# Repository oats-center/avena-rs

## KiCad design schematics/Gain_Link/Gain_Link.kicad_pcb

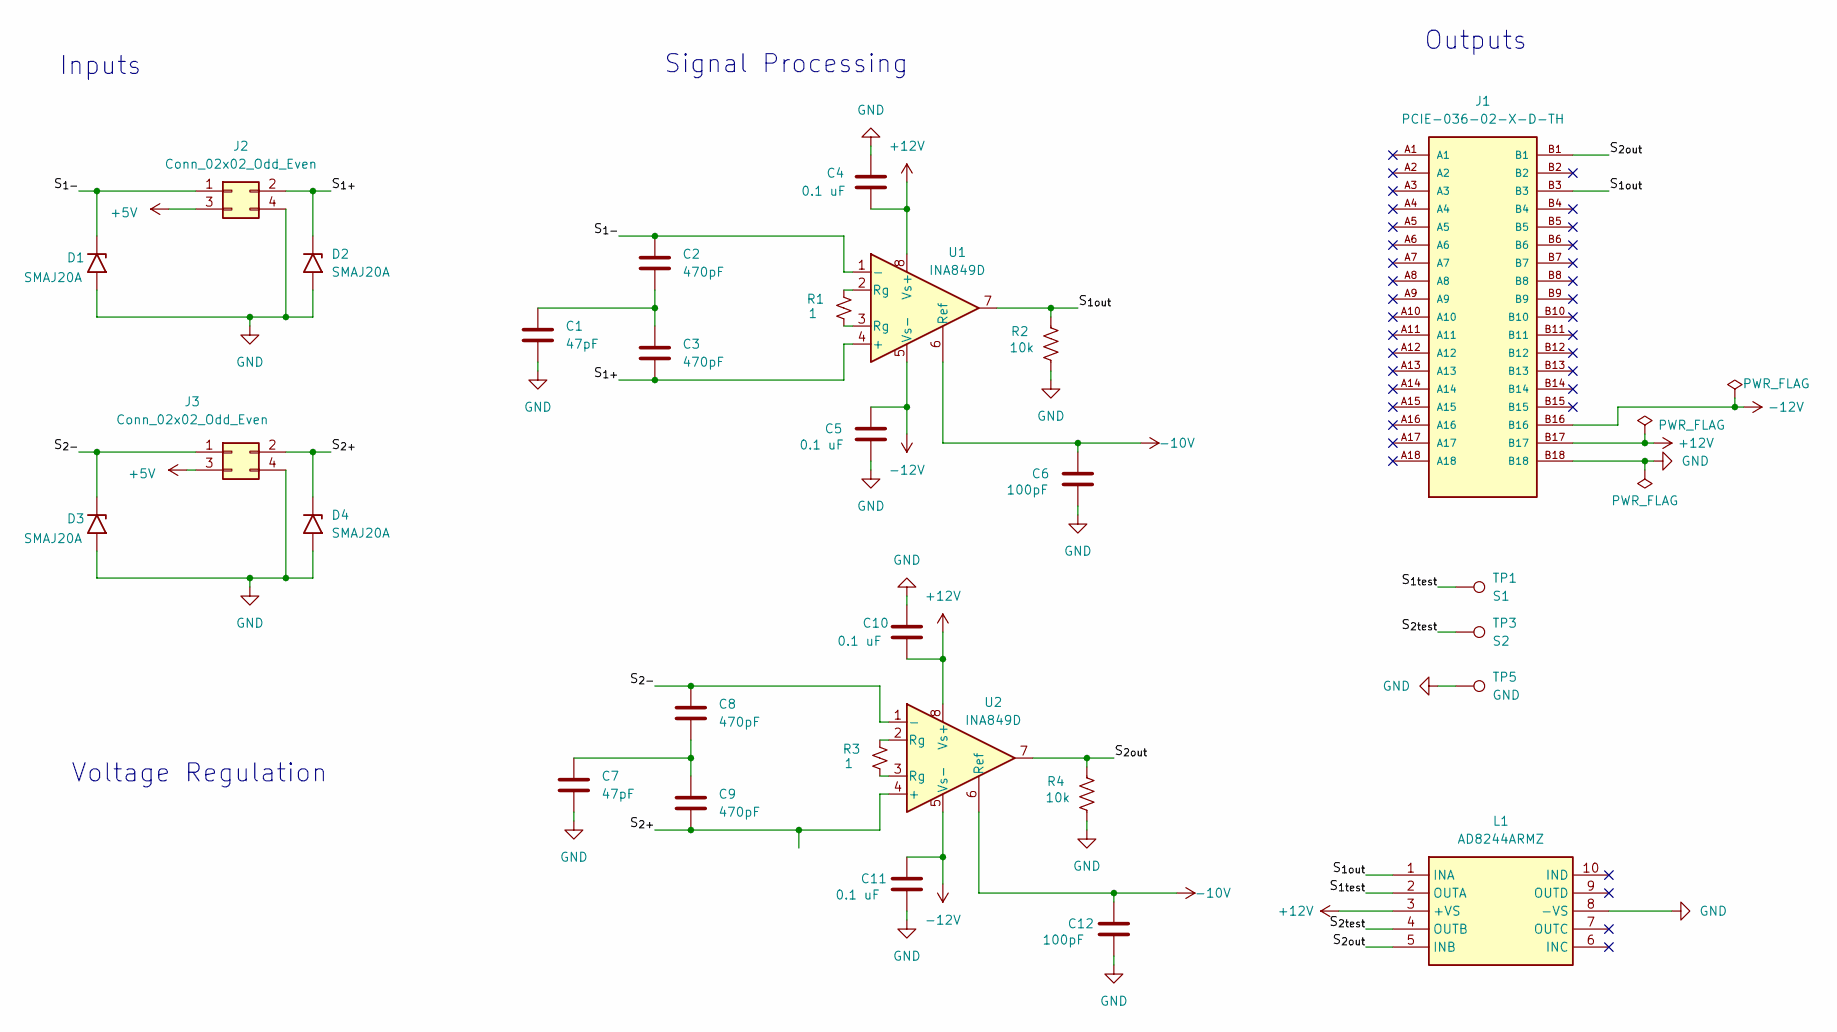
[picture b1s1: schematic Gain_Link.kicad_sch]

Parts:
C1, C7: 47pF; C_0603_1608Metric
C2, C3, C8, C9: 470pF; C_0603_1608Metric
C4, C5, C10, C11: 0.1 uF; C_0603_1608Metric
C6, C12: 100pF; C_0603_1608Metric
D1, D2, D3, D4: SMAJ20A; D_SMA
J1: PCIE-036-02-X-D-TH; BUS_PCIexpress_x1; PARTREV D
J2, J3: Conn_02x02_Odd_Even; PC-1053864
L1: AD8244ARMZ; Manufacturer_Part_Number AD8244ARMZ; Mouser Part Number 584-AD8244ARMZ
R1, R3: 1; R_0805_2012Metric
R2, R4: 10k; R_0805_2012Metric
TP1: S1; Keystone_5017
TP3: S2; Keystone_5017
TP5: GND; Keystone_5017
U1, U2: INA849D; INA849

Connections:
+5V: J2.3, J3.3
+12V: C4.1, C10.1, J1.B17, L1.3 (+VS), U1.8 (Vs+), U2.8 (Vs+)
-10V: C6.1, C12.1, U1.6 (Ref), U2.6 (Ref)
-12V: C5.1, C11.1, J1.B16, U1.5 (Vs-), U2.5 (Vs-)
/S_{1+}: C3.1, D2.1 (A1), J2.2, U1.4 (+)
/S_{1-}: C2.2, D1.1 (A1), J2.1, U1.1 (-)
/S_{1out}: J1.B3, L1.1 (INA), R2.2, U1.7
/S_{1test}: L1.2 (OUTA), TP1.1
/S_{2+}: C9.1, D4.1 (A1), J3.2, U2.4 (+)
/S_{2-}: C8.2, D3.1 (A1), J3.1, U2.1 (-)
/S_{2out}: J1.B1, L1.5 (INB), R4.2, U2.7
/S_{2test}: L1.4 (OUTB), TP3.1
GND: C1.1, C4.2, C5.2, C6.2, C7.1, C10.2, C11.2, C12.2, D1.2 (A2), D2.2 (A2), D3.2 (A2), D4.2 (A2), J1.B18, J2.4, J3.4, L1.8 (-VS), R2.1, R4.1, TP5.1
unnamed: C1.2, C2.1, C3.2
unnamed: C7.2, C8.1, C9.2
unnamed: R1.1, U1.2 (Rg)
unnamed: R1.2, U1.3 (Rg)
unnamed: R3.1, U2.2 (Rg)
unnamed: R3.2, U2.3 (Rg)

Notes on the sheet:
Voltage Regulation
Inputs
Signal Processing
Outputs

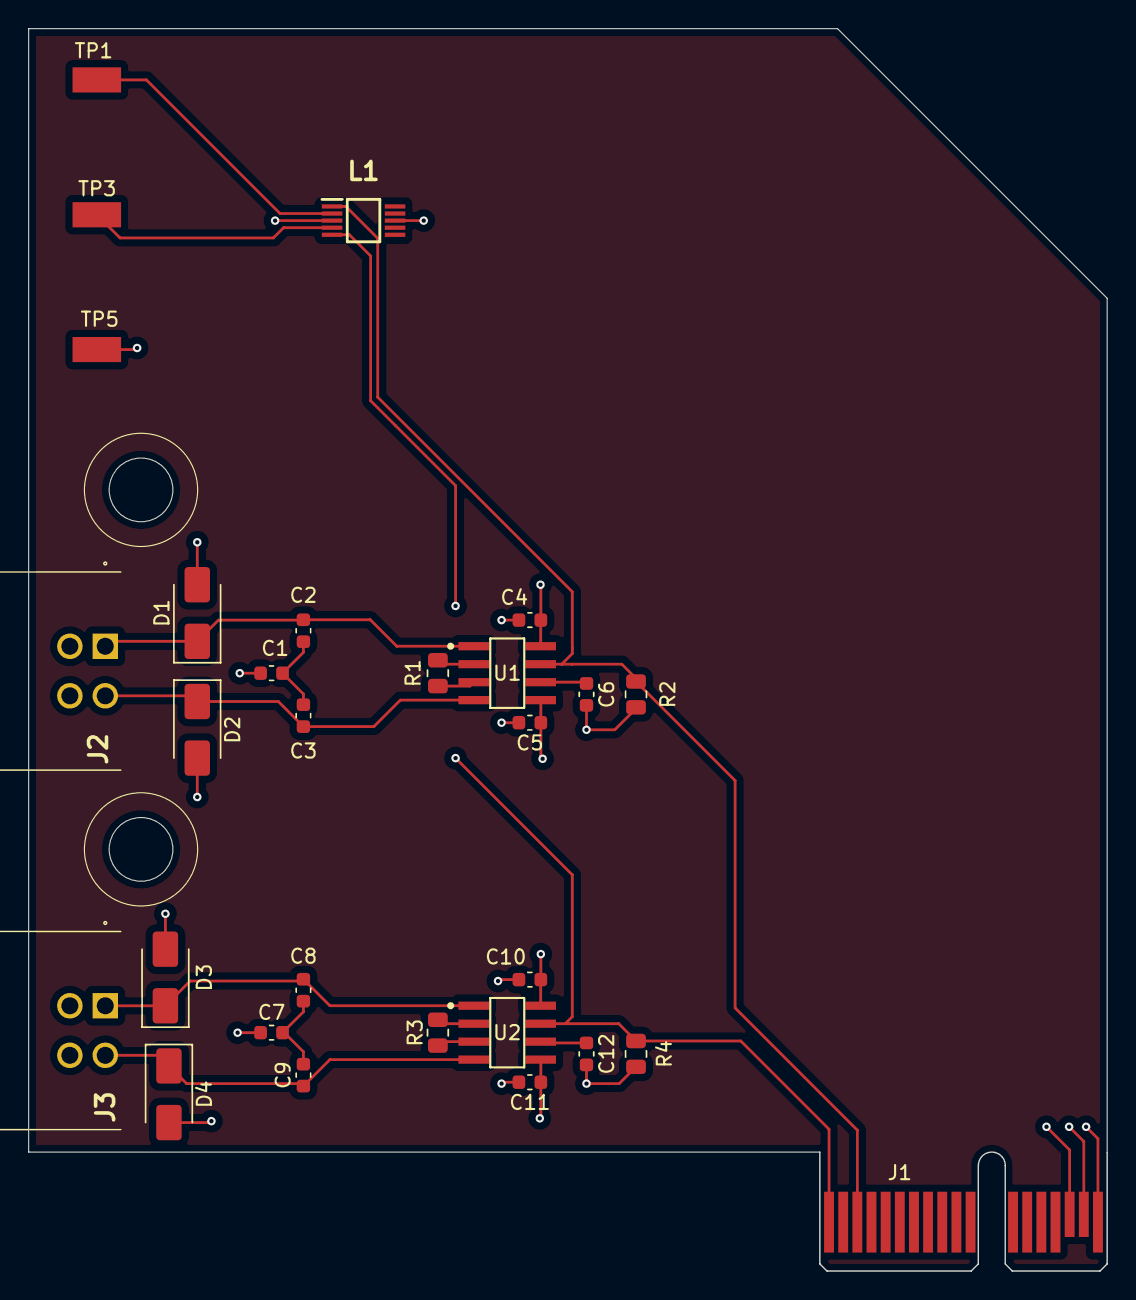
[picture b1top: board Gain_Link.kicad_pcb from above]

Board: 4 copper layers, 76.2 x 87.8 mm, 29 parts (0 on the bottom side), 19 nets.

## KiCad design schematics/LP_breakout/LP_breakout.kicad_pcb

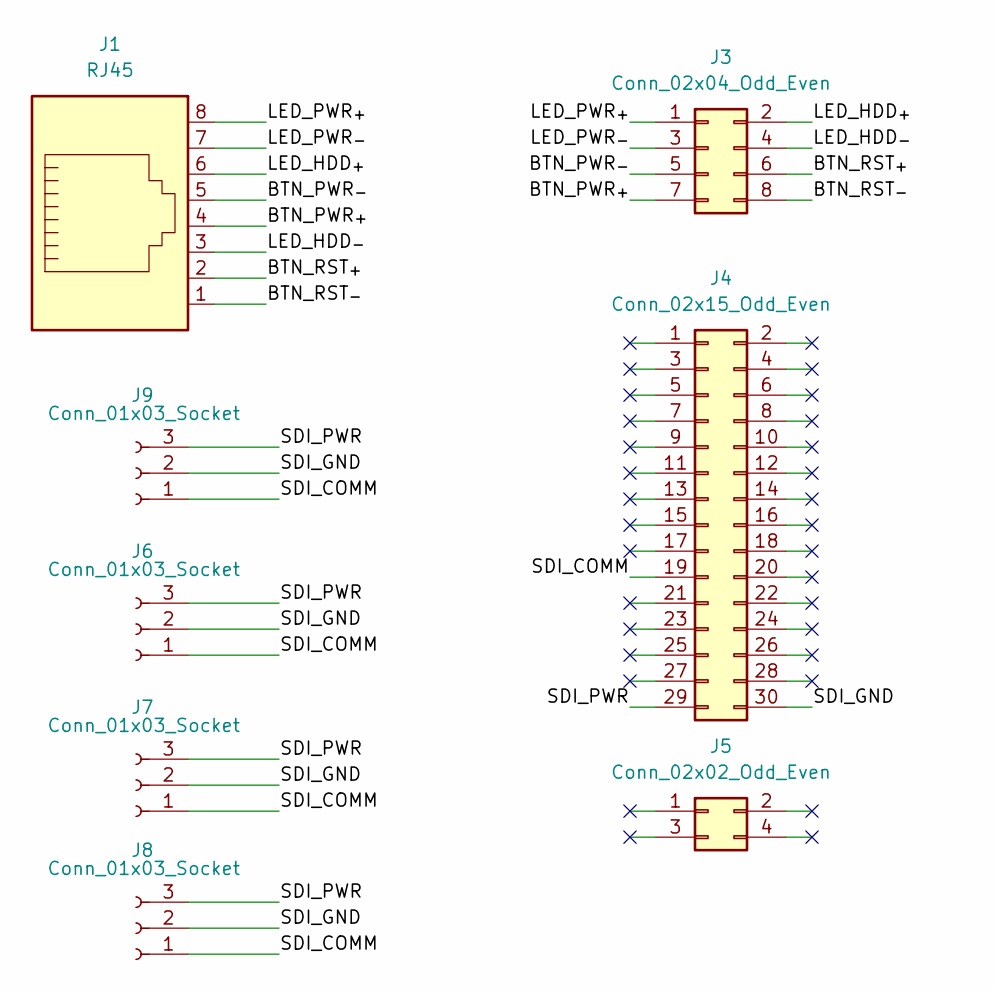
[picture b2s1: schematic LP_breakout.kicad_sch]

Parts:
J1: RJ45; RJ45_Amphenol_54602-x08_Horizontal
J3: Conn_02x04_Odd_Even; PinSocket_2x04_P2.54mm_Vertical
J4: Conn_02x15_Odd_Even; PinHeader_2x15_P2.54mm_Vertical
J5: Conn_02x02_Odd_Even; PinHeader_2x02_P2.54mm_Vertical
J6, J7, J8, J9: Conn_01x03_Socket; PC-1844223

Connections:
/BTN_PWR_{+}: J1.4, J3.7
/BTN_PWR_{-}: J1.5, J3.5
/BTN_RST_{+}: J1.2, J3.6
/BTN_RST_{-}: J1.1, J3.8
/LED_HDD_{+}: J1.6, J3.2
/LED_HDD_{-}: J1.3, J3.4
/LED_PWR_{+}: J1.8, J3.1
/LED_PWR_{-}: J1.7, J3.3
/SDI_COMM: J4.19, J6.1, J7.1, J8.1, J9.1
/SDI_GND: J4.30, J6.2, J7.2, J8.2, J9.2
/SDI_PWR: J4.29, J6.3, J7.3, J8.3, J9.3

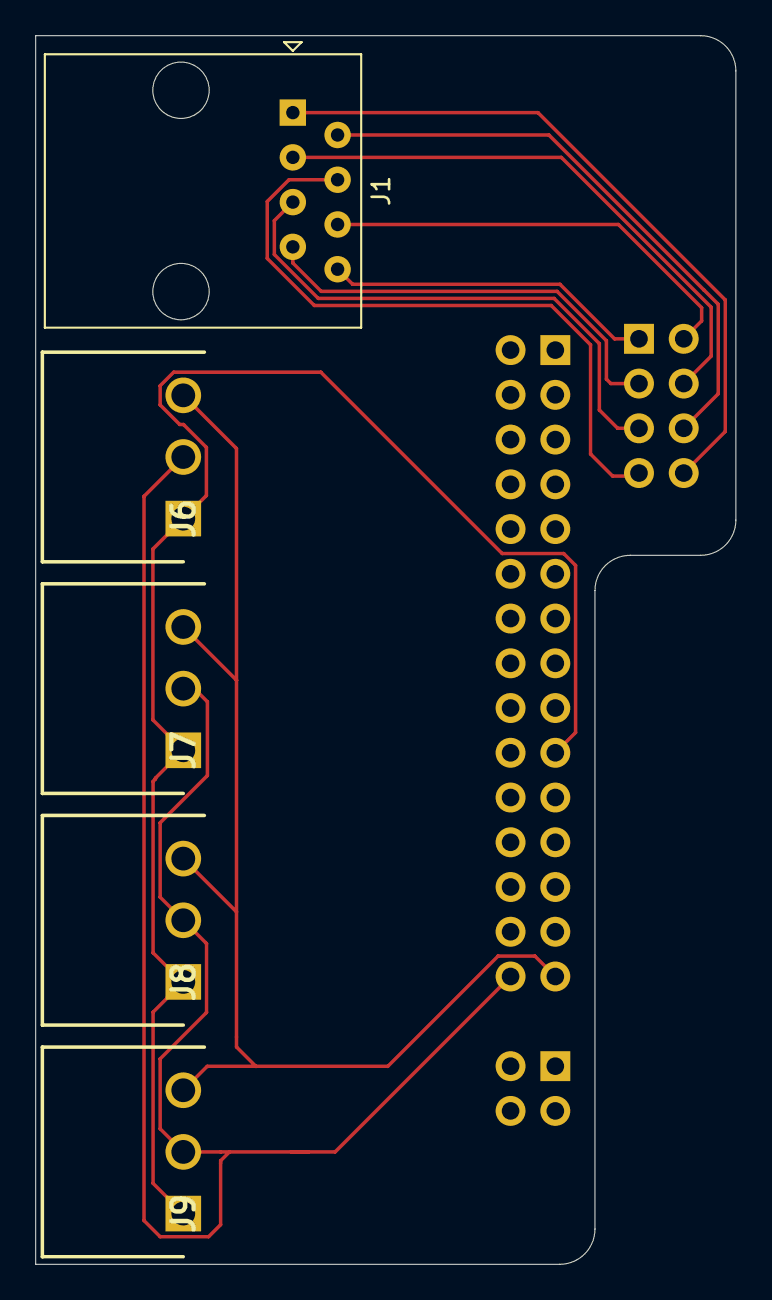
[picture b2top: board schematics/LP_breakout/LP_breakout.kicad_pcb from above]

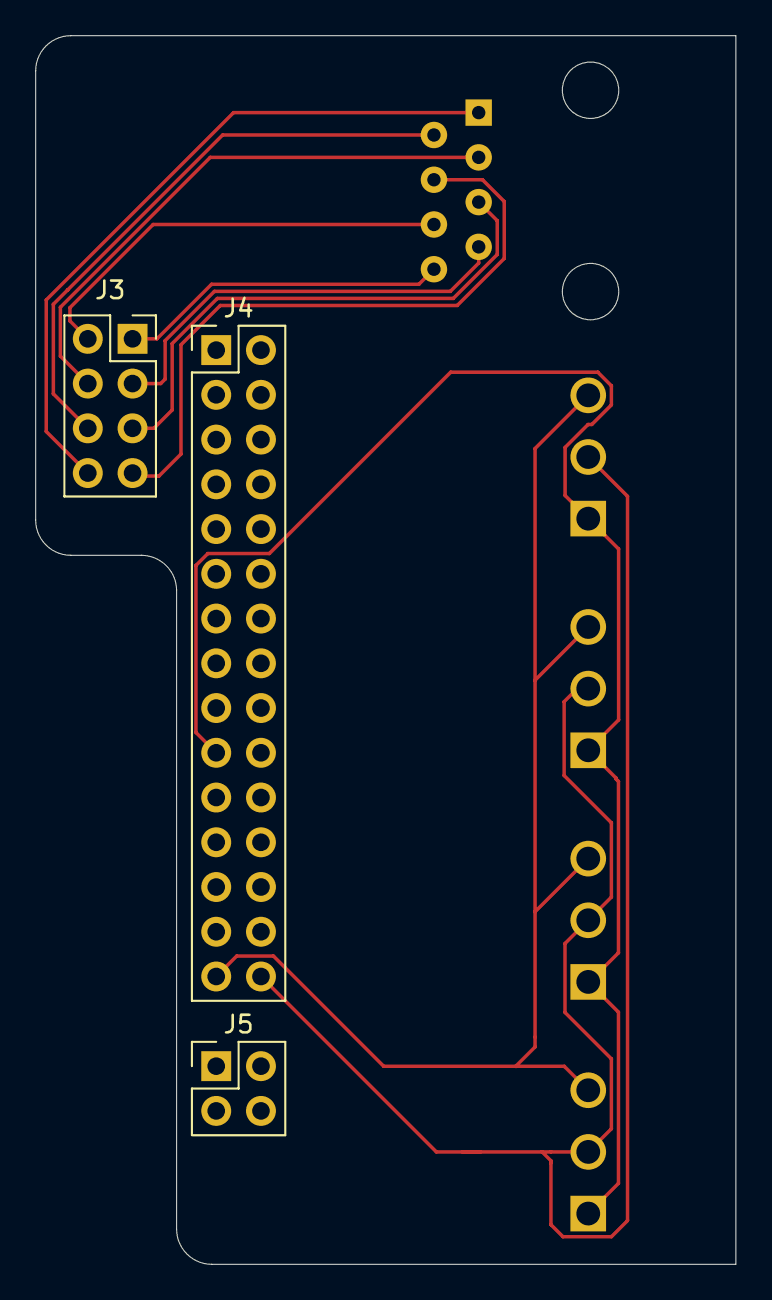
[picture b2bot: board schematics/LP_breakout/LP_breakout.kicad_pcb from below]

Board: 2 copper layers, 39.8 x 69.8 mm, 8 parts (3 on the bottom side), 11 nets.

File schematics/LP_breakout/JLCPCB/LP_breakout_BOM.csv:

Comment,Designator,Footprint
RJ45,J1,RJ45_Amphenol_54602-x08_Horizontal
P2.54mm_02x04 Pin_Socket,J3,"PinSocket_2x04_P2.54mm_Vertical"";1;""Conn_02x04_Odd_Even"
P2.54mm_02x15_Pin_Header,J4,"PinHeader_2x15_P2.54mm_Vertical"";1;""Conn_02x15_Odd_Even"
P2.54mm_02x02_Pin_Header,J5,"PinHeader_2x02_P2.54mm_Vertical"";1;""Conn_02x02_Odd_Even"
Phoenix Contact,J6,Conn_01x03_Socket
Phoenix Contact,J7,Conn_01x03_Socket
Phoenix Contact,J8,Conn_01x03_Socket
Phoenix Contact,J9,Conn_01x03_Socket

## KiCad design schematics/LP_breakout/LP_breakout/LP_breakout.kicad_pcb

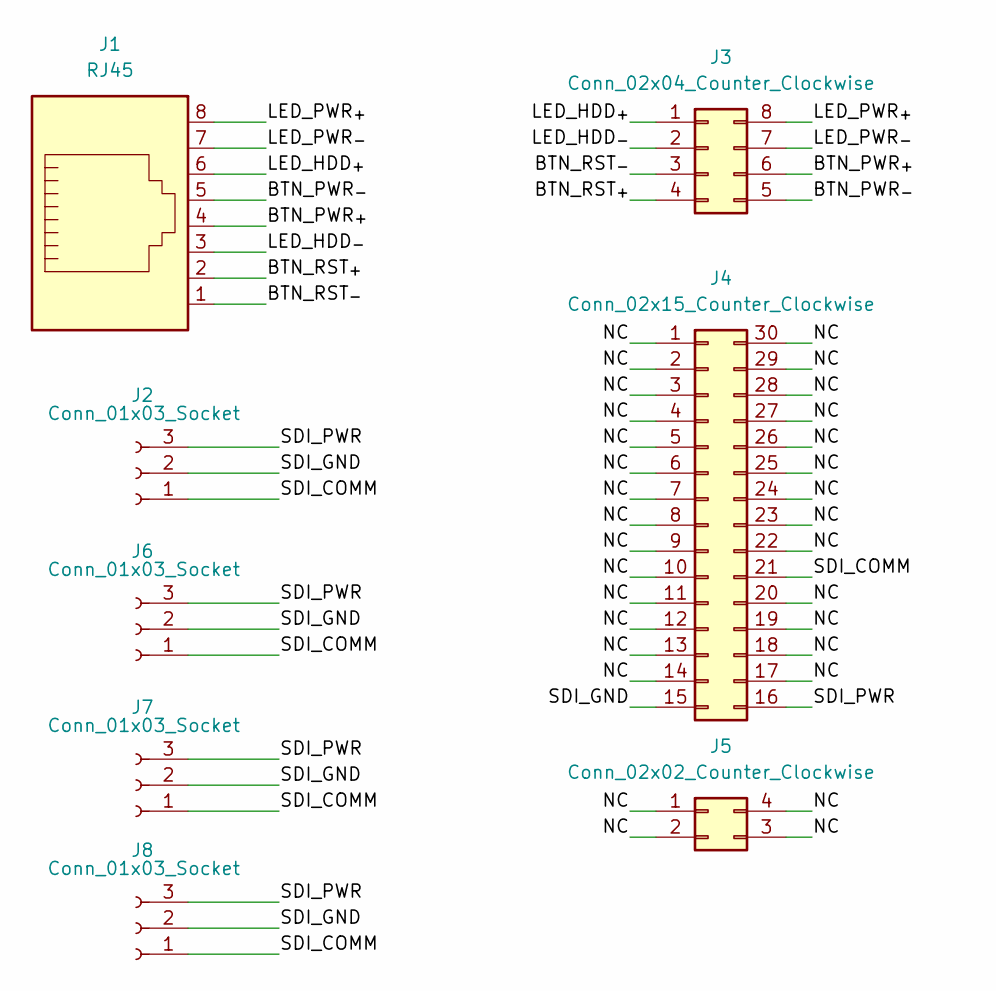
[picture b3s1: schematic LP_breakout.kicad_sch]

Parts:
J1: RJ45; RJ45_Amphenol_RJHSE538X
J2, J6, J7, J8: Conn_01x03_Socket; MC1,5_3-G-3,5
J3: Conn_02x04_Counter_Clockwise; PinSocket_2x04_P2.54mm_Vertical
J4: Conn_02x15_Counter_Clockwise; PinHeader_2x15_P2.54mm_Vertical
J5: Conn_02x02_Counter_Clockwise; PinHeader_2x02_P2.54mm_Vertical

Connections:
/BTN_PWR_{+}: J1.4, J3.6
/BTN_PWR_{-}: J1.5, J3.5
/BTN_RST_{+}: J1.2, J3.4
/BTN_RST_{-}: J1.1, J3.3
/LED_HDD_{+}: J1.6, J3.1
/LED_HDD_{-}: J1.3, J3.2
/LED_PWR_{+}: J1.8, J3.8
/LED_PWR_{-}: J1.7, J3.7
/NC: J4.1, J4.2, J4.3, J4.4, J4.5, J4.6, J4.7, J4.8, J4.9, J4.10, J4.11, J4.12, J4.13, J4.14, J4.17, J4.18, J4.19, J4.20, J4.22, J4.23, J4.24, J4.25, J4.26, J4.27, J4.28, J4.29, J4.30, J5.1, J5.2, J5.3, J5.4
/SDI_COMM: J2.1, J4.21, J6.1, J7.1, J8.1
/SDI_GND: J2.2, J4.15, J6.2, J7.2, J8.2
/SDI_PWR: J2.3, J4.16, J6.3, J7.3, J8.3

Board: 2 copper layers, 8 parts (0 on the bottom side), 12 nets, no tracks yet.

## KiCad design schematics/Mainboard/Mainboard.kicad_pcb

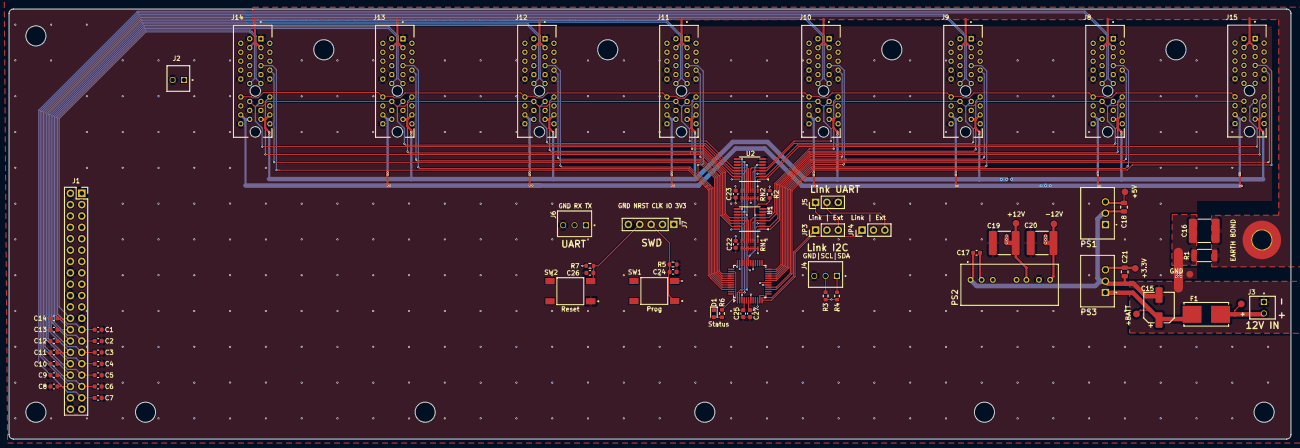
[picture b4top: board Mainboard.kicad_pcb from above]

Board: 4 copper layers, 286.5 x 96.1 mm, 72 parts (0 on the bottom side), 75 nets.

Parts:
C1, C2, C3, C4, C5, C6, C7, C8, C9, C10, C11, C12, C13, C14: 220p; C_0603_1608Metric
C15: 100u; CP_Elec_6.3x5.4
C16: 100n; C_2220_5750Metric
C17, C22, C23, C24, C25, C26, C27: 100n; C_0603_1608Metric
C18, C21: 10u; C_0805_2012Metric
C19, C20: 22u; C_2220_5750Metric
D1: Status; D_0603_1608Metric
F1: Fuse; 0154Series_LTF
H1: Chassis; MountingHole_4.3mm_M4_Pad_TopOnly
J1: LabJack T7; PinSocket_2x20_P2.54mm_Vertical
J2: JL_T7_PWR; TE_3-641215-2
J3: Battery; TE_3-641215-2
J4: Link I2C; TE_3-641215-3
J5: Link UART; PinHeader_1x03_P2.54mm_Vertical
J6: Mainboard UART; TE_3-641215-3
J7: SWD; PinHeader_1x05_P2.54mm_Vertical
J8, J9, J10, J11, J12, J13, J14, J15: LinkConnector; SAMTEC_PCIE-036-02-X-D-TH
JP3, JP4: Jumper_3_Bridged12; PinHeader_1x03_P2.54mm_Vertical
NT1: NetTie_3_Tee; NetTie-3_SMD_Pad2.0mm
PS1: R-78CK5.0-0.5; R78CK5005
PS2: DPBW06F-12
PS3: R-78CK3.3-0.5; R78CK3305
R1: 1M; R_2010_5025Metric
R2, R5, R7: 10k; R_0603_1608Metric
R3, R4: 47k; R_0603_1608Metric
R6: 270; R_0603_1608Metric
RN1, RN2: 10k; RESCAXS50P400X160X55-16N
SW1: BOOT0; SW_TS04-66-55-BK-260-SMT
SW2: RESET; SW_TS04-66-55-BK-260-SMT
TP1: Vbatt; TestPoint_Pad_D1.5mm
TP2: +BATT; TestPoint_Pad_D1.5mm
TP3: +5V; TestPoint_Pad_D1.5mm
TP4: +12V; TestPoint_Pad_D1.5mm
TP5: -12V; TestPoint_Pad_D1.5mm
TP6: +3.3V; TestPoint_Pad_D1.5mm
TP7: GND; TestPoint_Pad_D1.5mm
U1, U2: 74HC4051; TSSOP-16_4.4x5mm_P0.65mm
U3: STM32G0B1CBTx; LQFP-48_7x7mm_P0.5mm

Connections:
+3V3: C21.1, C22.1, C23.1, C25.1, C27.1, J7.1, J8.A14 (3V3), J8.B14 (3V3), J9.A9 (SLOT_ID0), J9.A14 (3V3), J9.B14 (3V3), J10.A14 (3V3), J10.B9 (SLOT_ID1), J10.B14 (3V3), J11.A9 (SLOT_ID0), J11.A14 (3V3), J11.B9 (SLOT_ID1), J11.B14 (3V3), J12.A14 (3V3), J12.B8 (SLOT_ID2), J12.B14 (3V3), J13.A9 (SLOT_ID0), J13.A14 (3V3), J13.B8 (SLOT_ID2), J13.B14 (3V3), J14.A14 (3V3), J14.B8 (SLOT_ID2), J14.B9 (SLOT_ID1), J14.B14 (3V3), J15.A9 (SLOT_ID0), J15.A14 (3V3), J15.B8 (SLOT_ID2), J15.B9 (SLOT_ID1), J15.B14 (3V3), PS3.3 (VOUT), R2.1, R3.1, R4.1, R7.1, RN1.1 (common), RN2.1 (common), SW1.2, TP6.1, U1.16 (VCC), U2.16 (VCC), U3.4 (VBAT), U3.6 (VDD)
+5V: C18.1, J2.1, J8.A2 (+5V), J8.B2 (+5V), J9.A2 (+5V), J9.B2 (+5V), J10.A2 (+5V), J10.B2 (+5V), J11.A2 (+5V), J11.B2 (+5V), J12.A2 (+5V), J12.B2 (+5V), J13.A2 (+5V), J13.B2 (+5V), J14.A2 (+5V), J14.B2 (+5V), J15.A2 (+5V), J15.B2 (+5V), PS1.3 (VOUT), TP3.1
+12V: C19.2, J8.A16 (+12V), J8.A17 (+12V), J9.A16 (+12V), J9.A17 (+12V), J10.A16 (+12V), J10.A17 (+12V), J11.A16 (+12V), J11.A17 (+12V), J12.A16 (+12V), J12.A17 (+12V), J13.A16 (+12V), J13.A17 (+12V), J14.A16 (+12V), J14.A17 (+12V), J15.A16 (+12V), J15.A17 (+12V), PS2.6 (+VOUT), TP4.1
+BATT: C15.1, C17.1, F1.2, PS1.1 (VIN), PS2.2 (+VIN), PS3.1 (VIN), TP2.1
-12V: C20.1, J8.B16 (-12V), J8.B17 (-12V), J9.B16 (-12V), J9.B17 (-12V), J10.B16 (-12V), J10.B17 (-12V), J11.B16 (-12V), J11.B17 (-12V), J12.B16 (-12V), J12.B17 (-12V), J13.B16 (-12V), J13.B17 (-12V), J14.B16 (-12V), J14.B17 (-12V), J15.B16 (-12V), J15.B17 (-12V), PS2.8 (-VOUT), TP5.1
/AIN_{0}: C7.1, J1.37, J8.A11 (ANALOG0)
/AIN_{1}: C8.2, J1.36, J8.B11 (ANALOG1)
/AIN_{2}: C6.1, J1.35, J9.A11 (ANALOG0)
/AIN_{3}: C9.2, J1.34, J9.B11 (ANALOG1)
/AIN_{4}: C5.1, J1.33, J10.A11 (ANALOG0)
/AIN_{5}: C10.2, J1.32, J10.B11 (ANALOG1)
/AIN_{6}: C4.1, J1.31, J11.A11 (ANALOG0)
/AIN_{7}: C11.2, J1.30, J11.B11 (ANALOG1)
/AIN_{8}: C3.1, J1.29, J12.A11 (ANALOG0)
/AIN_{9}: C12.2, J1.28, J12.B11 (ANALOG1)
/AIN_{10}: C2.1, J1.27, J13.A11 (ANALOG0)
/AIN_{11}: C13.2, J1.26, J13.B11 (ANALOG1)
/AIN_{12}: C1.1, J1.25, J14.A11 (ANALOG0)
/AIN_{13}: C14.2, J1.24, J14.B11 (ANALOG1)
/MCU/BOOT0/SWCLK: C24.1, J7.3, R5.1, SW1.1, U3.36 (PA14)
/MCU/EN1: J8.A8 (ENABLE), U3.22 (PB10)
/MCU/EN2: J9.A8 (ENABLE), U3.23 (PB11)
/MCU/EN3: J10.A8 (ENABLE), U3.24 (PB12)
/MCU/EN4: J11.A8 (ENABLE), U3.39 (PD1)
/MCU/EN5: J12.A8 (ENABLE), U3.40 (PD2)
/MCU/EN6: J13.A8 (ENABLE), U3.41 (PD3)
/MCU/EN7: J14.A8 (ENABLE), U3.42 (PB3)
/MCU/EN8: J15.A8 (ENABLE), U3.21 (PB2)
/MCU/LINK_CS: R2.2, U1.6 (~E), U2.6 (~E), U3.31 (PC7)
/MCU/LINK_CS0: U1.11 (S0), U2.11 (S0), U3.1 (PC13)
/MCU/LINK_CS1: U1.10 (S1), U2.10 (S1), U3.2 (PC14)
/MCU/LINK_CS2: U1.9 (S2), U2.9 (S2), U3.3 (PC15)
/MCU/LINK_RX: JP4.1 (A), U3.12 (PA1)
/MCU/LINK_TX: JP3.1 (A), U3.11 (PA0)
/MCU/MAIN_RX: J6.2, U3.32 (PA10/UCPD1_DBCC2)
/MCU/MAIN_TX: J6.1, U3.29 (PA9/UCPD1_DBCC1)
/MCU/NRST: C26.1, J7.4, R7.2, SW2.2, U3.10 (PF2)
/MCU/PROG1: J8.A7 (PROG), U3.16 (PA5)
/MCU/PROG2: J9.A7 (PROG), U3.19 (PB0)
/MCU/PROG3: J10.A7 (PROG), U3.20 (PB1)
/MCU/PROG4: J11.A7 (PROG), U3.43 (PB4)
/MCU/PROG5: J12.A7 (PROG), U3.44 (PB5)
/MCU/PROG6: J13.A7 (PROG), U3.45 (PB6)
/MCU/PROG7: J14.A7 (PROG), U3.46 (PB7)
/MCU/PROG8: J15.A7 (PROG), U3.15 (PA4)
/MCU/RX: JP4.2 (C), U2.3 (A)
/MCU/RX1: J8.A12 (UART_RX), RN1.3 (R2), U1.2 (A6)
/MCU/RX2: J9.A12 (UART_RX), RN1.4 (R3), U1.4 (A7)
/MCU/RX3: J10.A12 (UART_RX), RN1.5 (R4), U1.5 (A5)
/MCU/RX4: J11.A12 (UART_RX), RN1.6 (R5), U1.12 (A3)
/MCU/RX5: J12.A12 (UART_RX), RN1.7 (R6), U1.13 (A0)
/MCU/RX6: J13.A12 (UART_RX), RN1.8 (R7), U1.14 (A1)
/MCU/RX7: J14.A12 (UART_RX), RN1.9 (R8), U1.15 (A2)
/MCU/RX8: J15.A12 (UART_RX), RN1.2 (R1), U1.1 (A4)
/MCU/SCL: J4.2, J8.B12 (I2C_SCL), J9.B12 (I2C_SCL), J10.B12 (I2C_SCL), J11.B12 (I2C_SCL), J12.B12 (I2C_SCL), J13.B12 (I2C_SCL), J14.B12 (I2C_SCL), J15.B12 (I2C_SCL), R3.2, U3.17 (PA6)
/MCU/SDA: J4.1, J8.B13 (I2C_SDA), J9.B13 (I2C_SDA), J10.B13 (I2C_SDA), J11.B13 (I2C_SDA), J12.B13 (I2C_SDA), J13.B13 (I2C_SDA), J14.B13 (I2C_SDA), J15.B13 (I2C_SDA), R4.2, U3.18 (PA7)
/MCU/STATUS: R6.1, U3.38 (PD0)
/MCU/SWDIO: J7.2, U3.35 (PA13)
/MCU/TX: JP3.2 (C), U1.3 (A)
/MCU/TX1: J8.A13 (UART_TX), RN2.3 (R2), U2.2 (A6)
/MCU/TX2: J9.A13 (UART_TX), RN2.4 (R3), U2.4 (A7)
/MCU/TX3: J10.A13 (UART_TX), RN2.5 (R4), U2.5 (A5)
/MCU/TX4: J11.A13 (UART_TX), RN2.6 (R5), U2.12 (A3)
/MCU/TX5: J12.A13 (UART_TX), RN2.7 (R6), U2.13 (A0)
/MCU/TX6: J13.A13 (UART_TX), RN2.8 (R7), U2.14 (A1)
/MCU/TX7: J14.A13 (UART_TX), RN2.9 (R8), U2.15 (A2)
/MCU/TX8: J15.A13 (UART_TX), RN2.2 (R1), U2.1 (A4)
GND: C1.2, C2.2, C3.2, C4.2, C5.2, C6.2, C7.2, C8.1, C9.1, C10.1, C11.1, C12.1, C13.1, C14.1, C19.1, C20.2, C22.2, C23.2, C24.2, C25.2, C26.2, C27.2, D1.1 (K), J1.1, J1.2, J1.16, J1.20, J1.23, J1.38, J1.39, J1.40, J2.2, J4.3, J5.3, J6.3, J7.5, J8.A1 (GND), J8.A9 (SLOT_ID0), J8.A10 (GND), J8.A15 (GND), J8.A18 (GND), J8.B1 (GND), J8.B8 (SLOT_ID2), J8.B9 (SLOT_ID1), J8.B10 (GND), J8.B15 (GND), J8.B18 (GND), J9.A1 (GND), J9.A10 (GND), J9.A15 (GND), J9.A18 (GND), J9.B1 (GND), J9.B8 (SLOT_ID2), J9.B9 (SLOT_ID1), J9.B10 (GND), J9.B15 (GND), J9.B18 (GND), J10.A1 (GND), J10.A9 (SLOT_ID0), J10.A10 (GND), J10.A15 (GND), J10.A18 (GND), J10.B1 (GND), J10.B8 (SLOT_ID2), J10.B10 (GND), J10.B15 (GND), J10.B18 (GND), J11.A1 (GND), J11.A10 (GND), J11.A15 (GND), J11.A18 (GND), J11.B1 (GND), J11.B8 (SLOT_ID2), J11.B10 (GND), J11.B15 (GND), J11.B18 (GND), J12.A1 (GND), J12.A9 (SLOT_ID0), J12.A10 (GND), J12.A15 (GND), J12.A18 (GND), J12.B1 (GND), J12.B9 (SLOT_ID1), J12.B10 (GND), J12.B15 (GND), J12.B18 (GND), J13.A1 (GND), J13.A10 (GND), J13.A15 (GND), J13.A18 (GND), J13.B1 (GND), J13.B9 (SLOT_ID1), J13.B10 (GND), J13.B15 (GND), J13.B18 (GND), J14.A1 (GND), J14.A9 (SLOT_ID0), J14.A10 (GND), J14.A15 (GND), J14.A18 (GND), J14.B1 (GND), J14.B10 (GND), J14.B15 (GND), J14.B18 (GND), J15.A1 (GND), J15.A10 (GND), J15.A15 (GND), J15.A18 (GND), J15.B1 (GND), J15.B10 (GND), J15.B15 (GND), J15.B18 (GND), NT1.2, PS2.7 (COMMON), R5.2, SW2.1, TP7.1, U1.7 (VEE), U1.8 (GND), U2.7 (VEE), U2.8 (GND), U3.7 (VSS)
GNDBATT: C15.2, C17.2, C18.2, C21.2, J3.1, NT1.1, PS1.2 (GND), PS2.1 (-VIN), PS3.2 (GND)
GNDPWR: C16.2, H1.1, J8.A3 (PE), J8.B3 (PE), J9.A3 (PE), J9.B3 (PE), J10.A3 (PE), J10.B3 (PE), J11.A3 (PE), J11.B3 (PE), J12.A3 (PE), J12.B3 (PE), J13.A3 (PE), J13.B3 (PE), J14.A3 (PE), J14.B3 (PE), J15.A3 (PE), J15.B3 (PE), R1.2
unnamed: C16.1, NT1.3, R1.1
unnamed: D1.2 (A), R6.2
unnamed: F1.1, J3.2, TP1.1
unnamed: J5.1, JP3.3 (B)
unnamed: J5.2, JP4.3 (B)

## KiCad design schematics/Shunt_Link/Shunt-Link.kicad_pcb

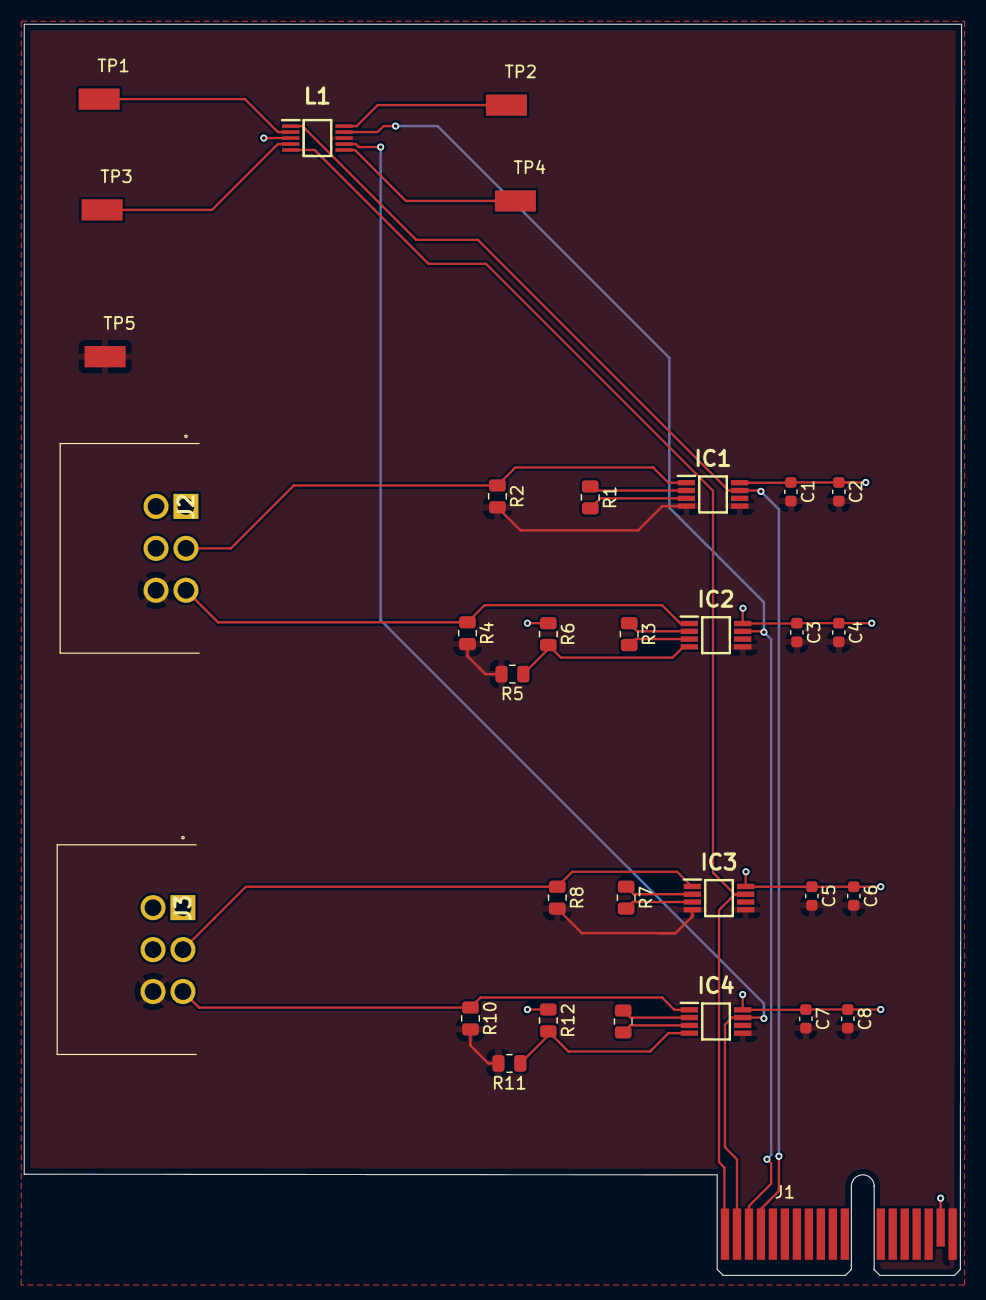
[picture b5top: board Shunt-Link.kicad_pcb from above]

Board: 2 copper layers, 78.2 x 104.4 mm, 33 parts (0 on the bottom side), 22 nets.

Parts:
C1, C3, C5, C7: 0.1 uF; C_0603_1608Metric
C2, C4, C6, C8: 10 uF; C_0603_1608Metric
IC1, IC2, IC3, IC4: AD8221TRMZ-EP; AD8221TRMZ
J1: PCIE-036-02-X-D-TH; BUS_PCIexpress_x1
J2, J3: Conn_02x03_Odd_Even; PC-1818517
L1: AD8244ARMZ
R1: R_{g1}; R_0805_2012Metric
R2, R8: R_{shunt}; R_0805_2012Metric
R3: R_{g2}; R_0805_2012Metric
R4, R5, R6, R10, R11, R12: R; R_0805_2012Metric
R7: R_{g3}; R_0805_2012Metric
R9: R_{g4}; R_0805_2012Metric
TP1: S1; Keystone_5017
TP2: T1; Keystone_5017
TP3: S2; Keystone_5017
TP4: T2; Keystone_5017
TP5: GND; Keystone_5017

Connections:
+12V: C1.1, C2.1, C3.1, C4.1, C5.1, C6.1, C7.1, C8.1, IC1.8 (+VS), IC2.8 (+VS), IC3.8 (+VS), IC4.8 (+VS), J1.B17, J2.1, J2.4, J3.1, J3.4, L1.3 (+VS), R6.1, R12.1
/+2V5: IC1.6 (REF), IC3.6 (REF)
/S_{1+}: IC1.1 (-IN), J2.2, R2.1
/S_{1out}: IC1.7 (VOUT), J1.B4, L1.1 (INA)
/S_{2+}: IC3.1 (-IN), J3.2, R8.1
/S_{2out}: IC3.7 (VOUT), J1.B1, L1.5 (INB)
/T_{1-}: IC2.1 (-IN), J2.3, R4.1
/T_{1out}: IC2.7 (VOUT), J1.B3, L1.9 (OUTD)
/T_{2-}: IC4.1 (-IN), J3.3, R10.1
/T_{2out}: IC4.7 (VOUT), J1.B2, L1.7 (OUTC)
/V_{ref}: IC2.6 (REF), IC4.6 (REF)
GND: C1.2, C2.2, C3.2, C4.2, C5.2, C6.2, C7.2, C8.2, IC1.4 (+IN), IC1.5 (-VS), IC2.5 (-VS), IC3.4 (+IN), IC3.5 (-VS), IC4.5 (-VS), J1.B18, J2.6, J3.6, L1.8 (-VS), R2.2, R4.2, R5.2, R8.2, R10.2, R11.2
unnamed: IC1.2 (RG_1), R1.1
unnamed: IC1.3 (RG_2), R1.2
unnamed: IC2.4 (+IN), R5.1, R6.2
unnamed: IC2.2 (RG_1), R3.1
unnamed: IC2.3 (RG_2), R3.2
unnamed: IC3.2 (RG_1), R7.1
unnamed: IC3.3 (RG_2), R7.2
unnamed: IC4.4 (+IN), R11.1, R12.2
unnamed: IC4.2 (RG_1), R9.1
unnamed: IC4.3 (RG_2), R9.2

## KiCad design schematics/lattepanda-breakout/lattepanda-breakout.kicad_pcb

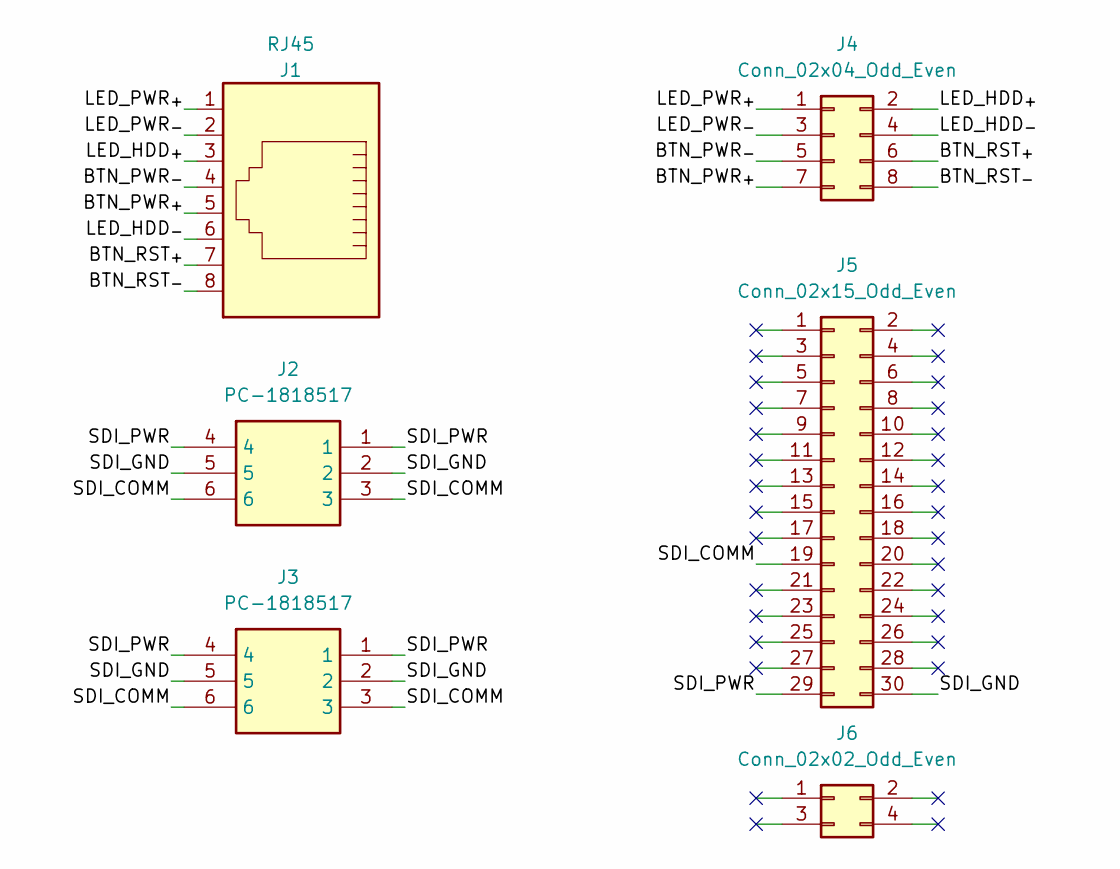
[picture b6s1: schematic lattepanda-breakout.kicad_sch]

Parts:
J1: RJ45; RJ45_Amphenol_54602-x08_Horizontal
J2, J3: PC-1818517; Manufacturer_Part_Number 1818517; Mouser Part Number 651-1818517
J4: Conn_02x04_Odd_Even; PinSocket_2x04_P2.54mm_Vertical
J5: Conn_02x15_Odd_Even; PinHeader_2x15_P2.54mm_Vertical
J6: Conn_02x02_Odd_Even; PinHeader_2x02_P2.54mm_Vertical

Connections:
/BTN_PWR_{+}: J1.5, J4.7
/BTN_PWR_{-}: J1.4, J4.5
/BTN_RST_{+}: J1.7, J4.6
/BTN_RST_{-}: J1.8, J4.8
/LED_HDD_{+}: J1.3, J4.2
/LED_HDD_{-}: J1.6, J4.4
/LED_PWR_{+}: J1.1, J4.1
/LED_PWR_{-}: J1.2, J4.3
/SDI_COMM: J2.3, J2.6, J3.3, J3.6, J5.19
/SDI_GND: J2.2, J2.5, J3.2, J3.5, J5.30
/SDI_PWR: J2.1, J2.4, J3.1, J3.4, J5.29

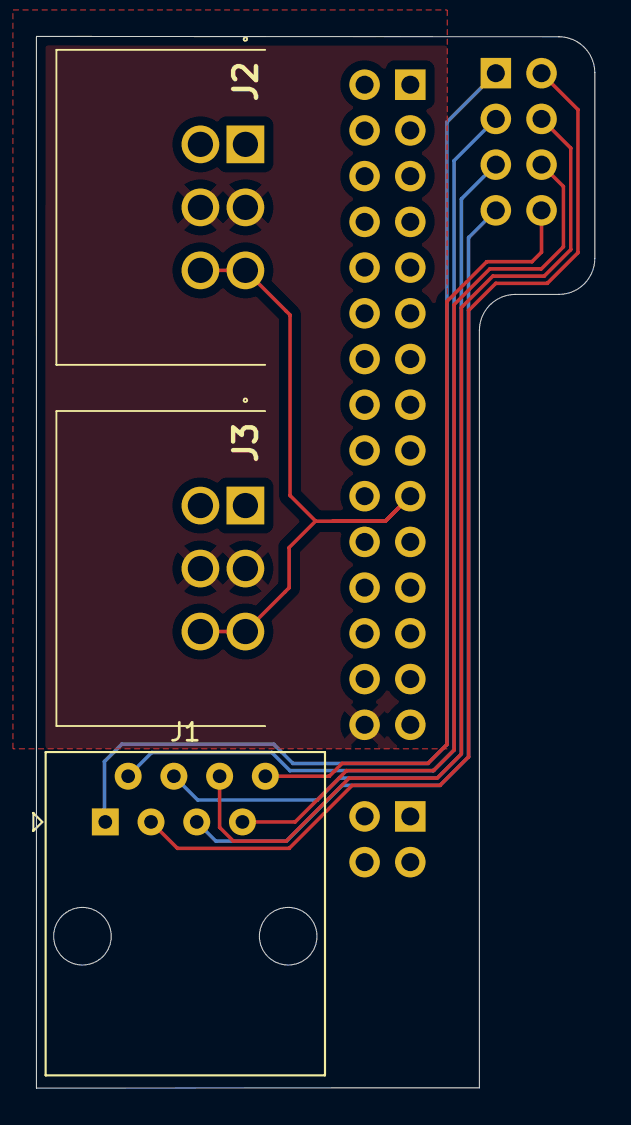
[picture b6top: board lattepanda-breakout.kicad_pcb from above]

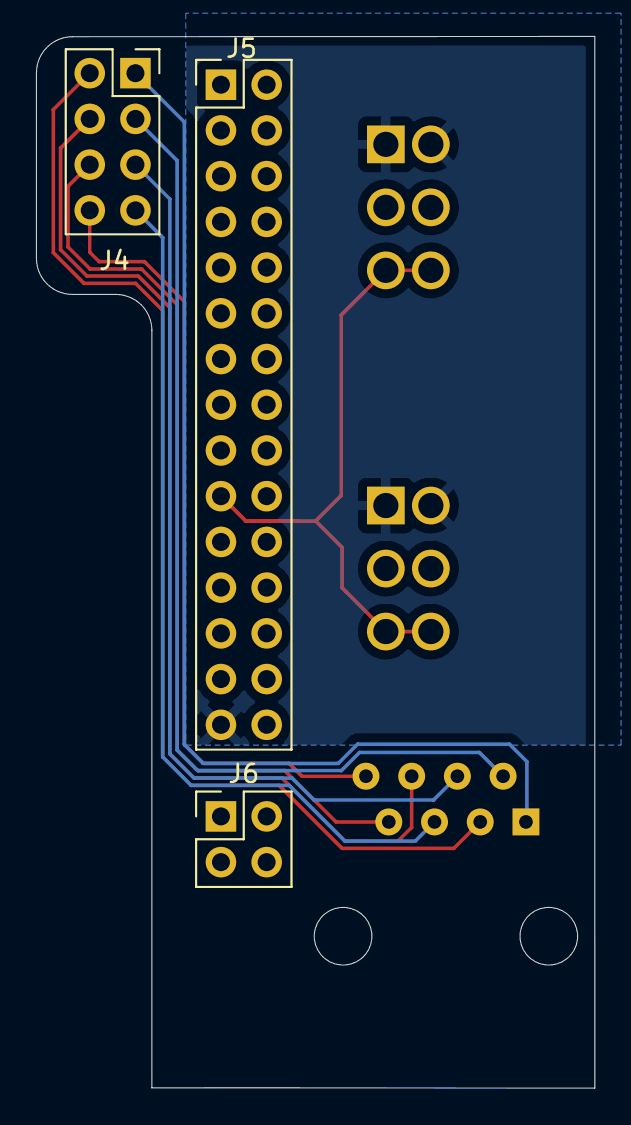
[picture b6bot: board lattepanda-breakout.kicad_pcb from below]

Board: 2 copper layers, 31.0 x 58.4 mm, 6 parts (3 on the bottom side), 11 nets.
